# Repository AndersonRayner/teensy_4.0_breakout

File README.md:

# Teensy 4.0 Breakout
Breakout Board for the Teensy 4.0. The connectors are designed to match the Pixhawk standard connectors, making it easy to interface with different sensors.

Features:
- 6 - 36 V Input
- 2 x Serial ports
- 1 x SPI with 2x CS
- 2 x I2C Ports
- 3 x PWM / ADC

Make sure to clone recursively!
```
git clone https://github.com/AndersonRayner/teensy_4.0_breakout.git --recursive
```

## Usage
- As the connectors are matching the Pixhawk standard, using the 0.1" headers means you can reverse plug! 
- Power for each of the output rails can be selected using the jumpers (between 3V3 and 5V)

## Contributions
As always, PRs are welcome!

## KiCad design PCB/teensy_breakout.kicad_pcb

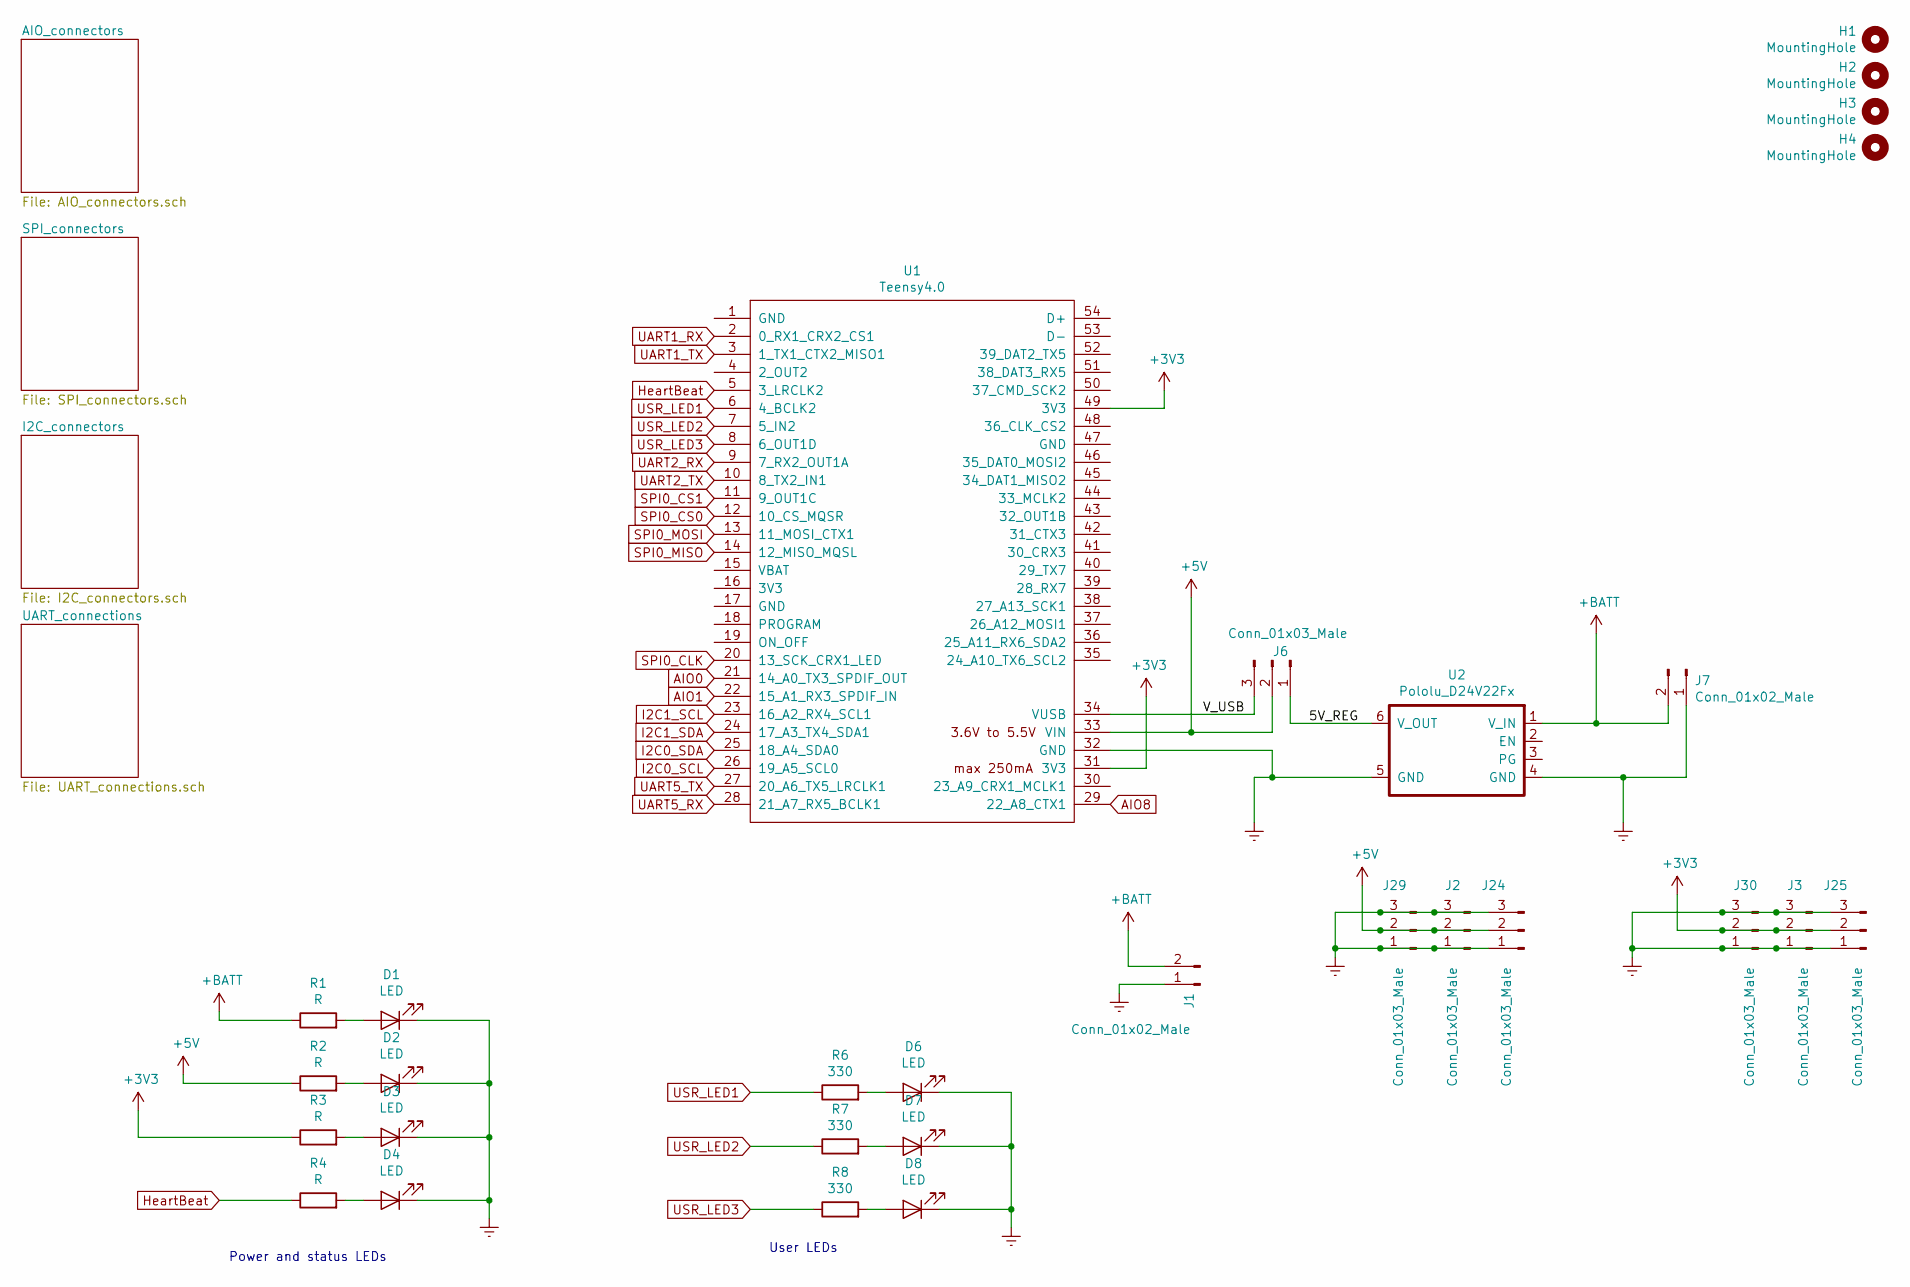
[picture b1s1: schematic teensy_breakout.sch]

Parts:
D1, D2, D3, D4, D6, D7, D8: LED; LED_0805_2012Metric_Pad1.15x1.40mm_HandSolder
H1, H2, H3, H4: MountingHole; MountingHole_3.2mm_M3
J1: Conn_01x02_Male; AMASS_XT30U-M_1x02_P5.0mm_Vertical
J2, J3, J6, J24, J25, J29, J30: Conn_01x03_Male; PinHeader_1x03_P2.54mm_Vertical
J7: Conn_01x02_Male; AMASS_XT30PW-M_1x02_P2.50mm_Horizontal
R1, R2, R3, R4: R; R_0805_2012Metric
R6, R7, R8: 330; R_0805_2012Metric
U1: Teensy4.0; Teensy40
U2: Pololu_D24V22Fx; Pololu_D24V22Fx_THT

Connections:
+3V3: J3.2, J25.2, J30.2, R3.1, U1.31 (3V3), U1.49 (3V3); also elsewhere on the board
+5V: J2.2, J6.2, J24.2, J29.2, R2.1, U1.33 (VIN); also elsewhere on the board
+BATT: J1.2, J7.2, R1.1, U2.1 (V_IN)
/5V_REG: J6.1, U2.6 (V_OUT)
/V_USB: J6.3, U1.34 (VUSB)
AIO0: U1.21 (14_A0_TX3_SPDIF_OUT); also elsewhere on the board
AIO1: U1.22 (15_A1_RX3_SPDIF_IN); also elsewhere on the board
AIO8: U1.29 (22_A8_CTX1); also elsewhere on the board
Earth: D1.1 (K), D2.1 (K), D3.1 (K), D4.1 (K), D6.1 (K), D7.1 (K), D8.1 (K), J1.1, J2.1, J2.3, J3.1, J3.3, J7.1, J24.1, J24.3, J25.1, J25.3, J29.1, J29.3, J30.1, J30.3, U1.32 (GND), U2.4 (GND), U2.5 (GND); also elsewhere on the board
HeartBeat: R4.1, U1.5 (3_LRCLK2)
I2C0_SCL: U1.26 (19_A5_SCL0); also elsewhere on the board
I2C0_SDA: U1.25 (18_A4_SDA0); also elsewhere on the board
I2C1_SCL: U1.23 (16_A2_RX4_SCL1); also elsewhere on the board
I2C1_SDA: U1.24 (17_A3_TX4_SDA1); also elsewhere on the board
unnamed: D1.2 (A), R1.2
unnamed: D2.2 (A), R2.2
unnamed: D3.2 (A), R3.2
unnamed: D4.2 (A), R4.2
unnamed: D6.2 (A), R6.2
unnamed: D7.2 (A), R7.2
unnamed: D8.2 (A), R8.2
SPI0_CLK: U1.20 (13_SCK_CRX1_LED); also elsewhere on the board
SPI0_CS0: U1.12 (10_CS_MQSR); also elsewhere on the board
SPI0_CS1: U1.11 (9_OUT1C); also elsewhere on the board
SPI0_MISO: U1.14 (12_MISO_MQSL); also elsewhere on the board
SPI0_MOSI: U1.13 (11_MOSI_CTX1); also elsewhere on the board
UART1_RX: U1.2 (0_RX1_CRX2_CS1); also elsewhere on the board
UART1_TX: U1.3 (1_TX1_CTX2_MISO1); also elsewhere on the board
UART2_RX: U1.9 (7_RX2_OUT1A); also elsewhere on the board
UART2_TX: U1.10 (8_TX2_IN1); also elsewhere on the board
UART5_RX: U1.28 (21_A7_RX5_BCLK1); also elsewhere on the board
UART5_TX: U1.27 (20_A6_TX5_LRCLK1); also elsewhere on the board
USR_LED1: R6.1, U1.6 (4_BCLK2)
USR_LED2: R7.1, U1.7 (5_IN2)
USR_LED3: R8.1, U1.8 (6_OUT1D)

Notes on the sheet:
Power and status LEDs
User LEDs

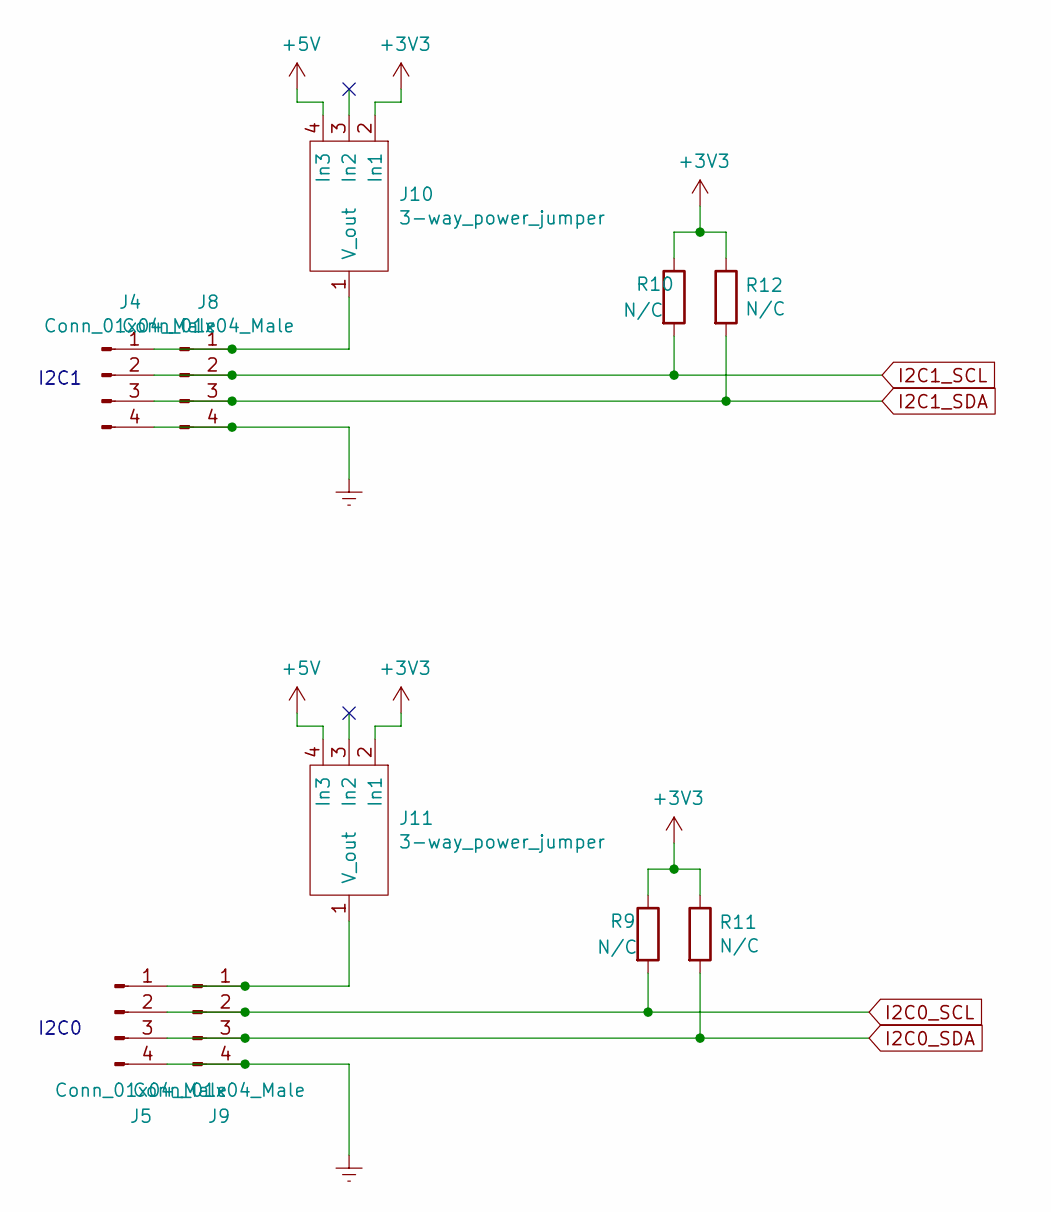
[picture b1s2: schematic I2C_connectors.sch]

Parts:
J4, J5: Conn_01x04_Male; PinSocket_1x04_P2.54mm_Vertical
J8, J9: Conn_01x04_Male; JST_GH_BM04B-GHS-TBT_1x04-1MP_P1.25mm_Vertical
J10, J11: 3-way_power_jumper
R9, R10, R11, R12: N/C; R_0805_2012Metric_Pad1.15x1.40mm_HandSolder

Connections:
+3V3: J10.2 (In1), J11.2 (In1), R9.1, R10.1, R11.1, R12.1; also elsewhere on the board
+5V: J10.4 (In3), J11.4 (In3); also elsewhere on the board
Earth: J4.4, J5.4, J8.4, J9.4; also elsewhere on the board
I2C0_SCL: J5.2, J9.2, R9.2; also elsewhere on the board
I2C0_SDA: J5.3, J9.3, R11.2; also elsewhere on the board
I2C1_SCL: J4.2, J8.2, R10.2; also elsewhere on the board
I2C1_SDA: J4.3, J8.3, R12.2; also elsewhere on the board
unnamed: J4.1, J8.1, J10.1 (V_out)
unnamed: J5.1, J9.1, J11.1 (V_out)

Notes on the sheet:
I2C1
I2C0

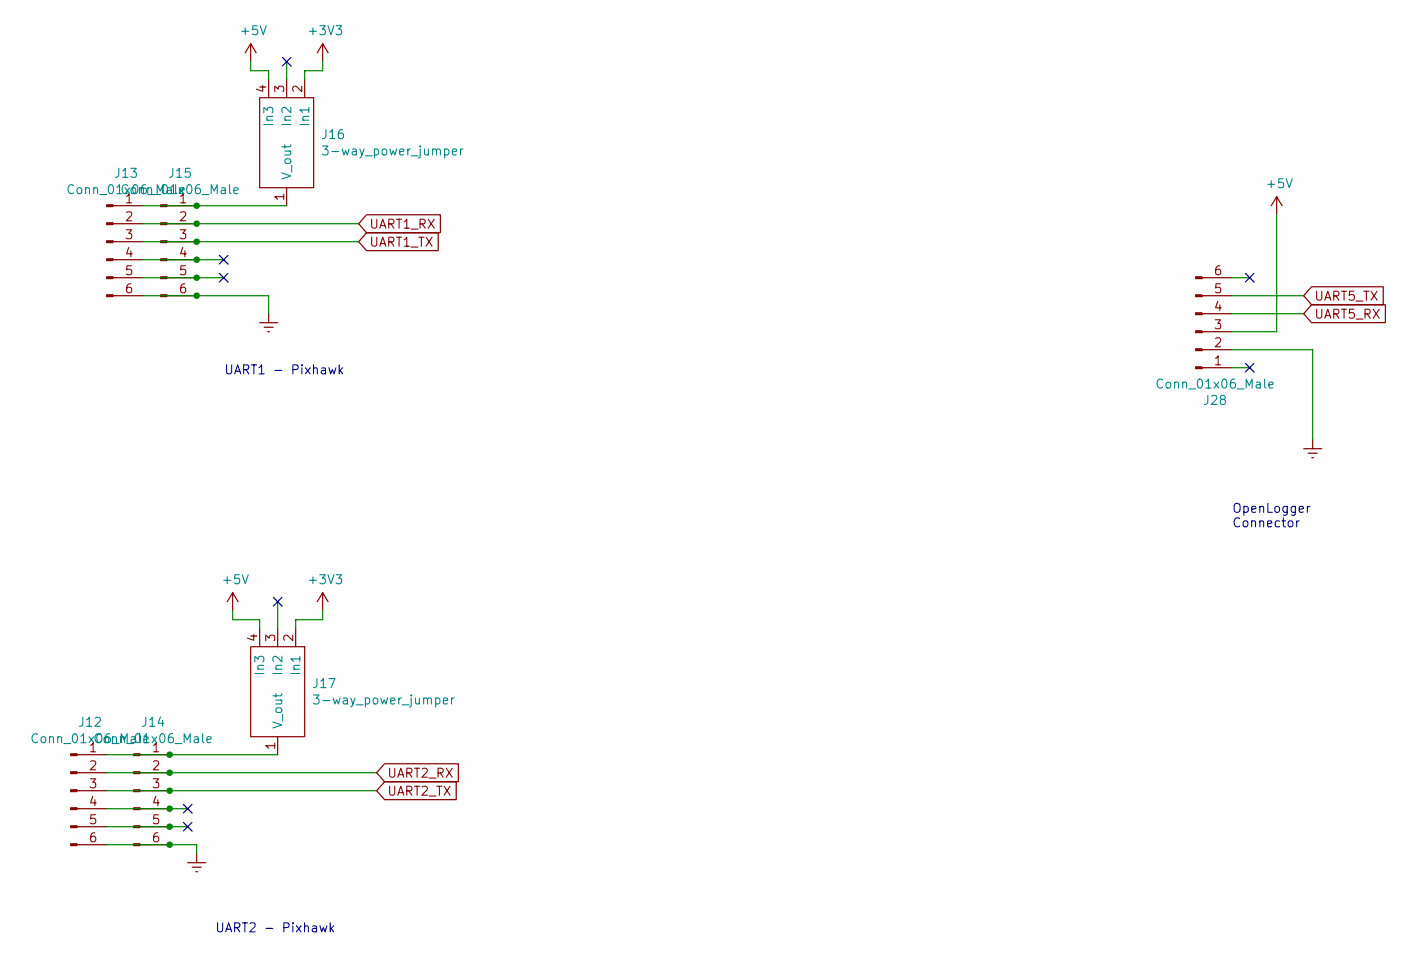
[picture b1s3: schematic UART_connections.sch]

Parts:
J12, J13, J28: Conn_01x06_Male; PinSocket_1x06_P2.54mm_Vertical
J14, J15: Conn_01x06_Male; JST_GH_BM06B-GHS-TBT_1x06-1MP_P1.25mm_Vertical
J16, J17: 3-way_power_jumper

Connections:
+3V3: J16.2 (In1), J17.2 (In1); also elsewhere on the board
+5V: J16.4 (In3), J17.4 (In3), J28.3; also elsewhere on the board
Earth: J12.6, J13.6, J14.6, J15.6, J28.2; also elsewhere on the board
unnamed: J12.1, J14.1, J17.1 (V_out)
unnamed: J12.4, J14.4
unnamed: J12.5, J14.5
unnamed: J13.1, J15.1, J16.1 (V_out)
unnamed: J13.4, J15.4
unnamed: J13.5, J15.5
UART1_RX: J13.2, J15.2; also elsewhere on the board
UART1_TX: J13.3, J15.3; also elsewhere on the board
UART2_RX: J12.2, J14.2; also elsewhere on the board
UART2_TX: J12.3, J14.3; also elsewhere on the board
UART5_RX: J28.4; also elsewhere on the board
UART5_TX: J28.5; also elsewhere on the board

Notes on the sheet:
UART2 - Pixhawk
UART1 - Pixhawk
OpenLogger Connector

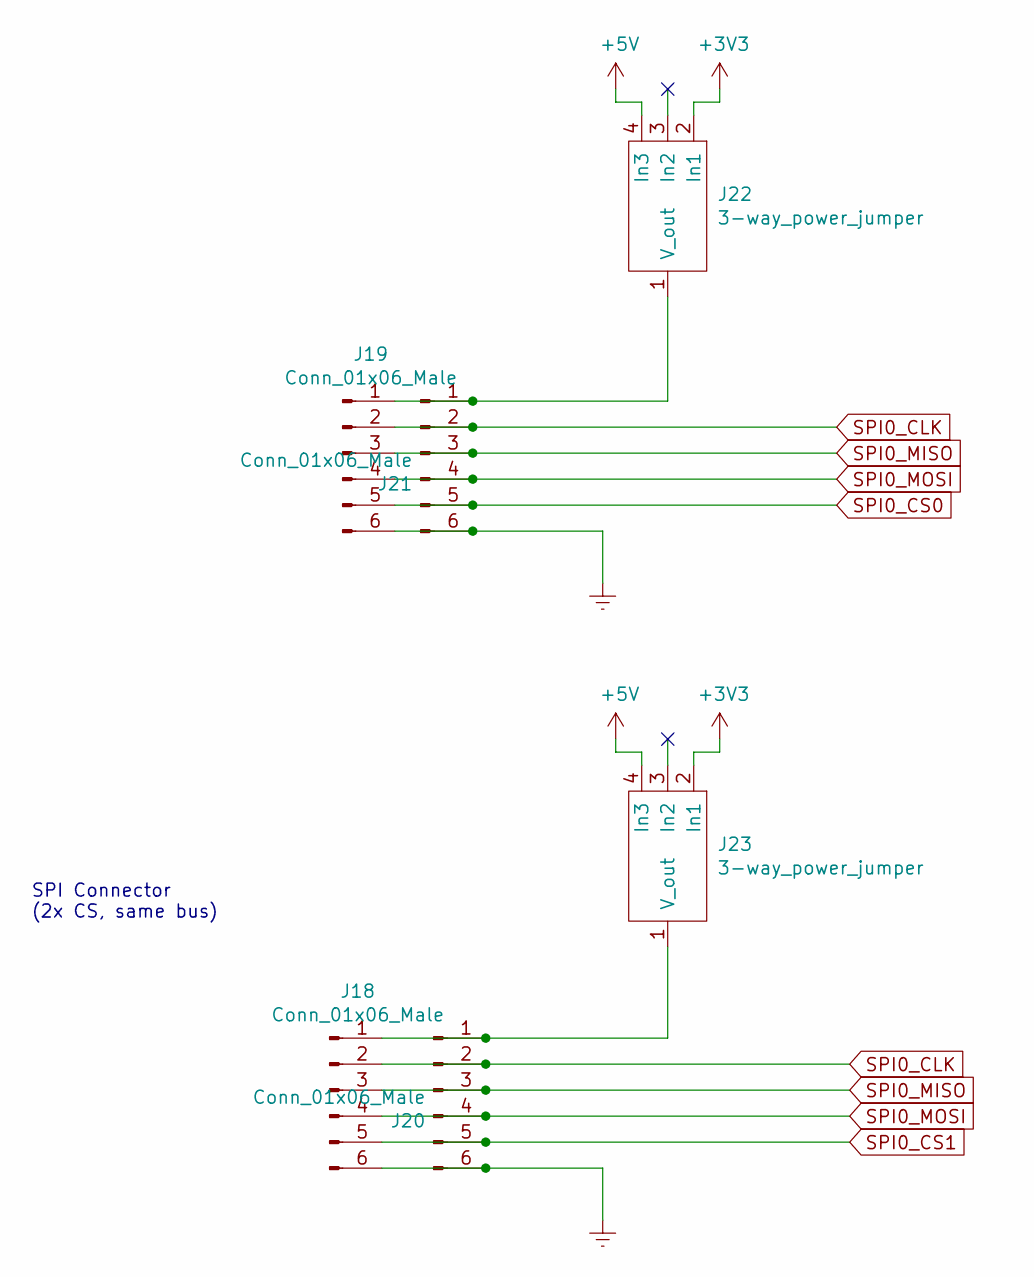
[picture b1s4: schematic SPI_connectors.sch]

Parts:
J18, J19: Conn_01x06_Male; PinSocket_1x06_P2.54mm_Vertical
J20, J21: Conn_01x06_Male; JST_GH_BM06B-GHS-TBT_1x06-1MP_P1.25mm_Vertical
J22, J23: 3-way_power_jumper

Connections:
+3V3: J22.2 (In1), J23.2 (In1); also elsewhere on the board
+5V: J22.4 (In3), J23.4 (In3); also elsewhere on the board
Earth: J18.6, J19.6, J20.6, J21.6; also elsewhere on the board
unnamed: J18.1, J20.1, J23.1 (V_out)
unnamed: J19.1, J21.1, J22.1 (V_out)
SPI0_CLK: J18.2, J19.2, J20.2, J21.2; also elsewhere on the board
SPI0_CS0: J19.5, J21.5; also elsewhere on the board
SPI0_CS1: J18.5, J20.5; also elsewhere on the board
SPI0_MISO: J18.3, J19.3, J20.3, J21.3; also elsewhere on the board
SPI0_MOSI: J18.4, J19.4, J20.4, J21.4; also elsewhere on the board

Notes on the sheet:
SPI Connector (2x CS, same bus)

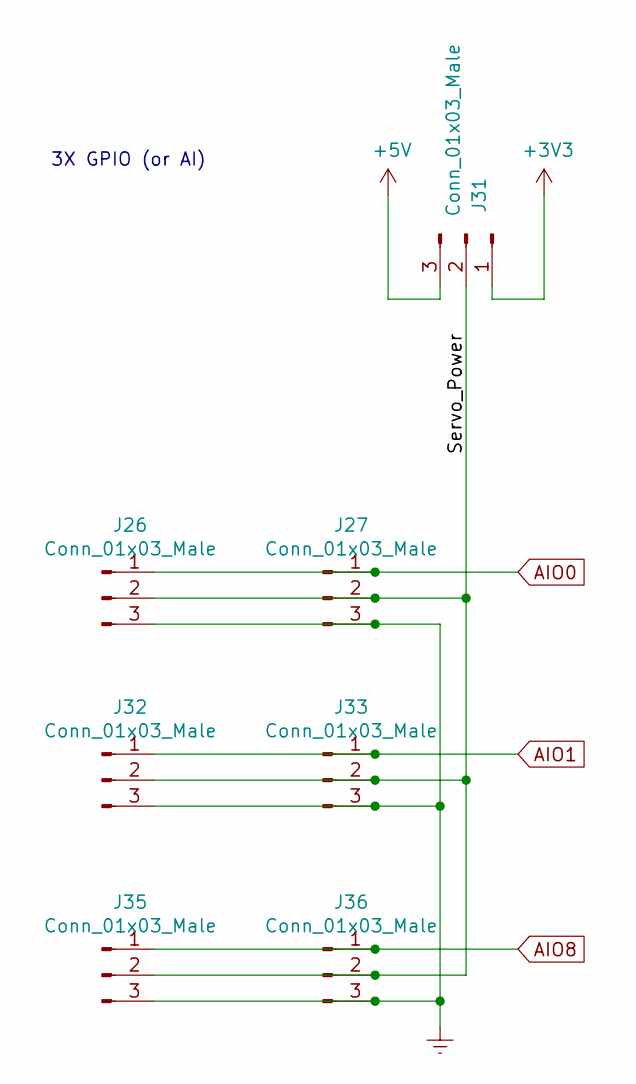
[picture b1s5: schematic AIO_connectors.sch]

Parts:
J26, J31, J32, J35: Conn_01x03_Male; PinSocket_1x03_P2.54mm_Vertical
J27, J33, J36: Conn_01x03_Male; JST_GH_BM03B-GHS-TBT_1x03-1MP_P1.25mm_Vertical

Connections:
+3V3: J31.1; also elsewhere on the board
+5V: J31.3; also elsewhere on the board
/AIO_connectors/Servo_Power: J26.2, J27.2, J31.2, J32.2, J33.2, J35.2, J36.2
AIO0: J26.1, J27.1; also elsewhere on the board
AIO1: J32.1, J33.1; also elsewhere on the board
AIO8: J35.1, J36.1; also elsewhere on the board
Earth: J26.3, J27.3, J32.3, J33.3, J35.3, J36.3; also elsewhere on the board

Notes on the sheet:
3X GPIO (or AI)

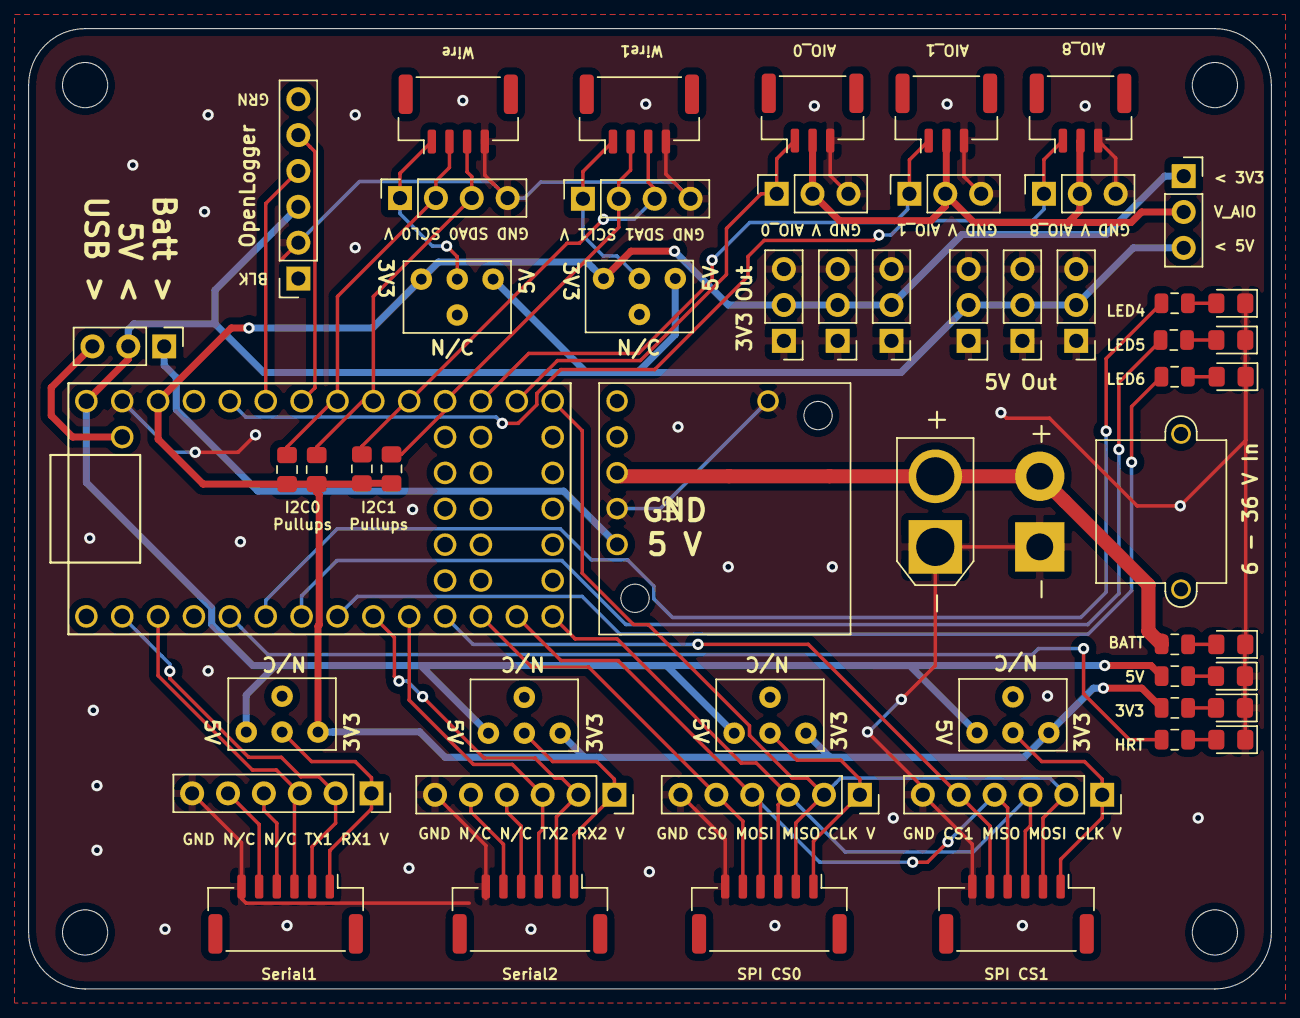
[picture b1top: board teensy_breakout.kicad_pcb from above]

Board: 2 copper layers, 88.0 x 68.0 mm, 59 parts (0 on the bottom side), 46 nets.

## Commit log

2021-04-30 Add image
2021-05-15 Fixed the GPS example
2021-05-31 better image
2021-12-29 Fixing all the paths
2021-12-29 Relative path
2021-12-29 Submodule update
2022-01-20 Fixed the labelling on the SPI bus
2022-01-20 Updated the version number
2023-09-15 Updated to add PDF and CAN test script
